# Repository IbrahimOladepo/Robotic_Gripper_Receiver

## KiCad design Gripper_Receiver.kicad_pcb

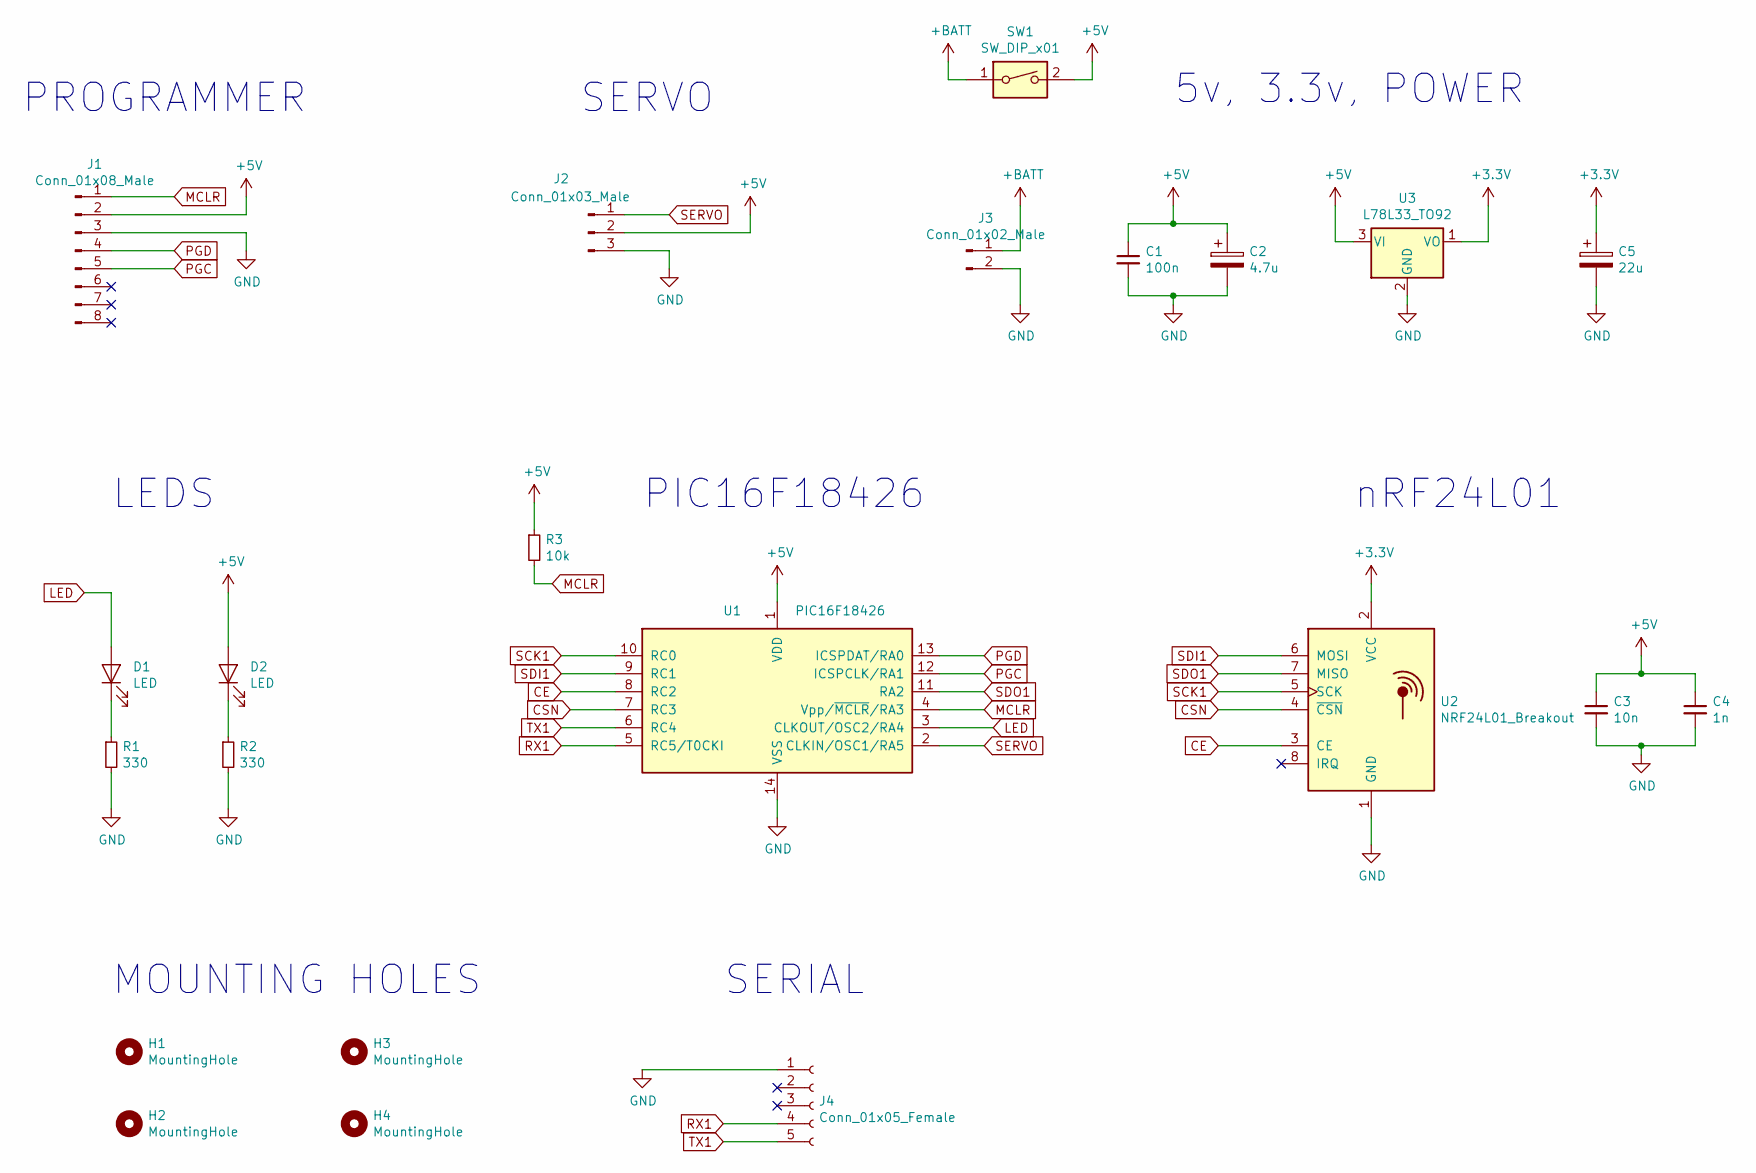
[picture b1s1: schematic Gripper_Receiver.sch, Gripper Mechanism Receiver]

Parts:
C1: 100n; C_Disc_D8.0mm_W2.5mm_P5.00mm
C2: 4.7u; CP_Radial_D5.0mm_P2.50mm
C3: 10n; C_Disc_D8.0mm_W2.5mm_P5.00mm
C4: 1n; C_Disc_D8.0mm_W2.5mm_P5.00mm
C5: 22u; CP_Radial_D5.0mm_P2.50mm
D1, D2: LED; LED_D4.0mm
H1, H2, H3, H4: MountingHole; MountingHole_3.2mm_M3
J1: Conn_01x08_Male; PinHeader_1x08_P2.54mm_Vertical
J2: Conn_01x03_Male; PinHeader_1x03_P2.54mm_Vertical
J3: Conn_01x02_Male; PinHeader_1x02_P2.54mm_Vertical
J4: Conn_01x05_Female; PinSocket_1x05_P2.54mm_Vertical
R1, R2: 330; R_Axial_DIN0204_L3.6mm_D1.6mm_P5.08mm_Horizontal
R3: 10k; R_Axial_DIN0204_L3.6mm_D1.6mm_P5.08mm_Horizontal
SW1: SW_DIP_x01; SolderWirePad_1x02_P3.81mm_Drill0.8mm
U1: PIC16F18426; DIP-14_W7.62mm_LongPads
U2: NRF24L01_Breakout; PinHeader_2x04_P2.54mm_Vertical
U3: L78L33_TO92; TO-92_Inline

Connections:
+3V3: C5.1, U2.2 (VCC), U3.1 (VO)
+5V: C1.1, C2.1, C3.1, C4.1, D2.2 (A), J1.2, J2.2, R3.1, SW1.2, U1.1 (VDD), U3.3 (VI)
+BATT: J3.1, SW1.1
CE: U1.8 (RC2), U2.3 (CE)
CSN: U1.7 (RC3), U2.4 (~CSN)
GND: C1.2, C2.2, C3.2, C4.2, C5.2, J1.3, J2.3, J3.2, J4.1, R1.2, R2.2, U1.14 (VSS), U2.1 (GND), U3.2 (GND)
LED: D1.2 (A), U1.3 (CLKOUT/OSC2/RA4)
MCLR: J1.1, R3.2, U1.4 (Vpp/~MCLR~/RA3)
unnamed: D1.1 (K), R1.1
unnamed: D2.1 (K), R2.1
PGC: J1.5, U1.12 (ICSPCLK/RA1)
PGD: J1.4, U1.13 (ICSPDAT/RA0)
RX1: J4.4, U1.5 (RC5/T0CKI)
SCK1: U1.10 (RC0), U2.5 (SCK)
SDI1: U1.9 (RC1), U2.6 (MOSI)
SDO1: U1.11 (RA2), U2.7 (MISO)
SERVO: J2.1, U1.2 (CLKIN/OSC1/RA5)
TX1: J4.5, U1.6 (RC4)

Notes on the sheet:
nRF24L01
5v, 3.3v, POWER
SERVO
PROGRAMMER
PIC16F18426
MOUNTING HOLES
LEDS
SERIAL

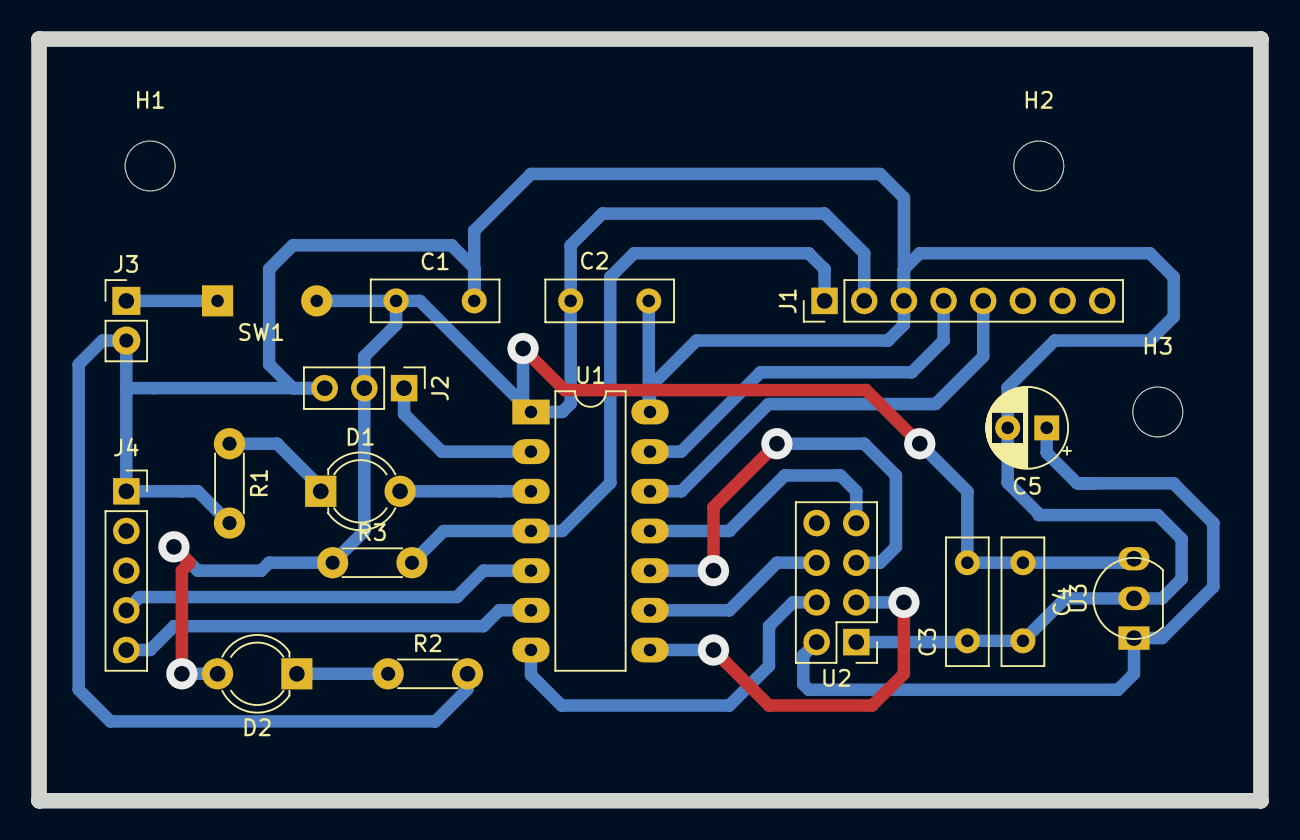
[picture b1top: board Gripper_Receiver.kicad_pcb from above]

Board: 2 copper layers, 78.2 x 48.8 mm, 21 parts (0 on the bottom side), 18 nets.

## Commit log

2024-03-04 Initial Commit to GitHub
